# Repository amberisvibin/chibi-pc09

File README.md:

# chibi pc-09

## Archived!

This repo has been archived, and the different parts have been migrated to other repos.

The PCB for prototype 1 has been moved to https://gitea.ambersplace.net/chibi/pc09-prototype-1

The firmware has been moved to https://gitea.ambersplace.net/chibi/chibi-firmware

## Description

The PC-09 will be a 6309 based microcomputer with an MMU using 74HC670 register files and dual 16550 UARTs. The plan is to eventually add uPD7220 graphics and PS/2 mouse and keyboard.

The two 74HC670s will take the top 4 bits of the address bus and expand them to 8 bits, turning the 16 bit cpu address space into a 20 bit address space capable of addressing 1MB of memory. Memory pages are 4KB. Being a register file, any page can be mapped to any slot, allowing complex memory management schemes.

The 16550 UART is capable of interrupt driven operation with FIFOs, allowing for characters to be processed in batches rather than individually, minimizing task switch delays. They also support hardware flow control, and some versions can automatically assert RTS when the FIFO is nearing full.

The uPD7220 graphics are very powerful, allowing 16 colors at 640x480, but it is a complex chip to get working. It will be left for a later date.

The solution for PS/2 keyboard and mouse have not yet been decided.

## Progress

I had started wiring together a board for prototyping, but it was destroyed in hurricane Helene. I am now recreating it in schematic form in order to order a PCB.

Prototype 1 is currently in progress. It will be a much simpler system. It will have no MMU, just the CPU, some RAM, some ROM, and the UART.

The PCB and parts for Prototype #1 have been ordered, and assembly will begin soon. Initial test code is now available in the code/ directory.

Assembly is in progress.

## License

This project is licensed under the MIT license. This applies to both the hardware (schematics, bill of materials, pcb layouts) and documentation. This does *not* apply to the datasheets/ directory or code/assist09/. Those files belong to their respective copyright holders.

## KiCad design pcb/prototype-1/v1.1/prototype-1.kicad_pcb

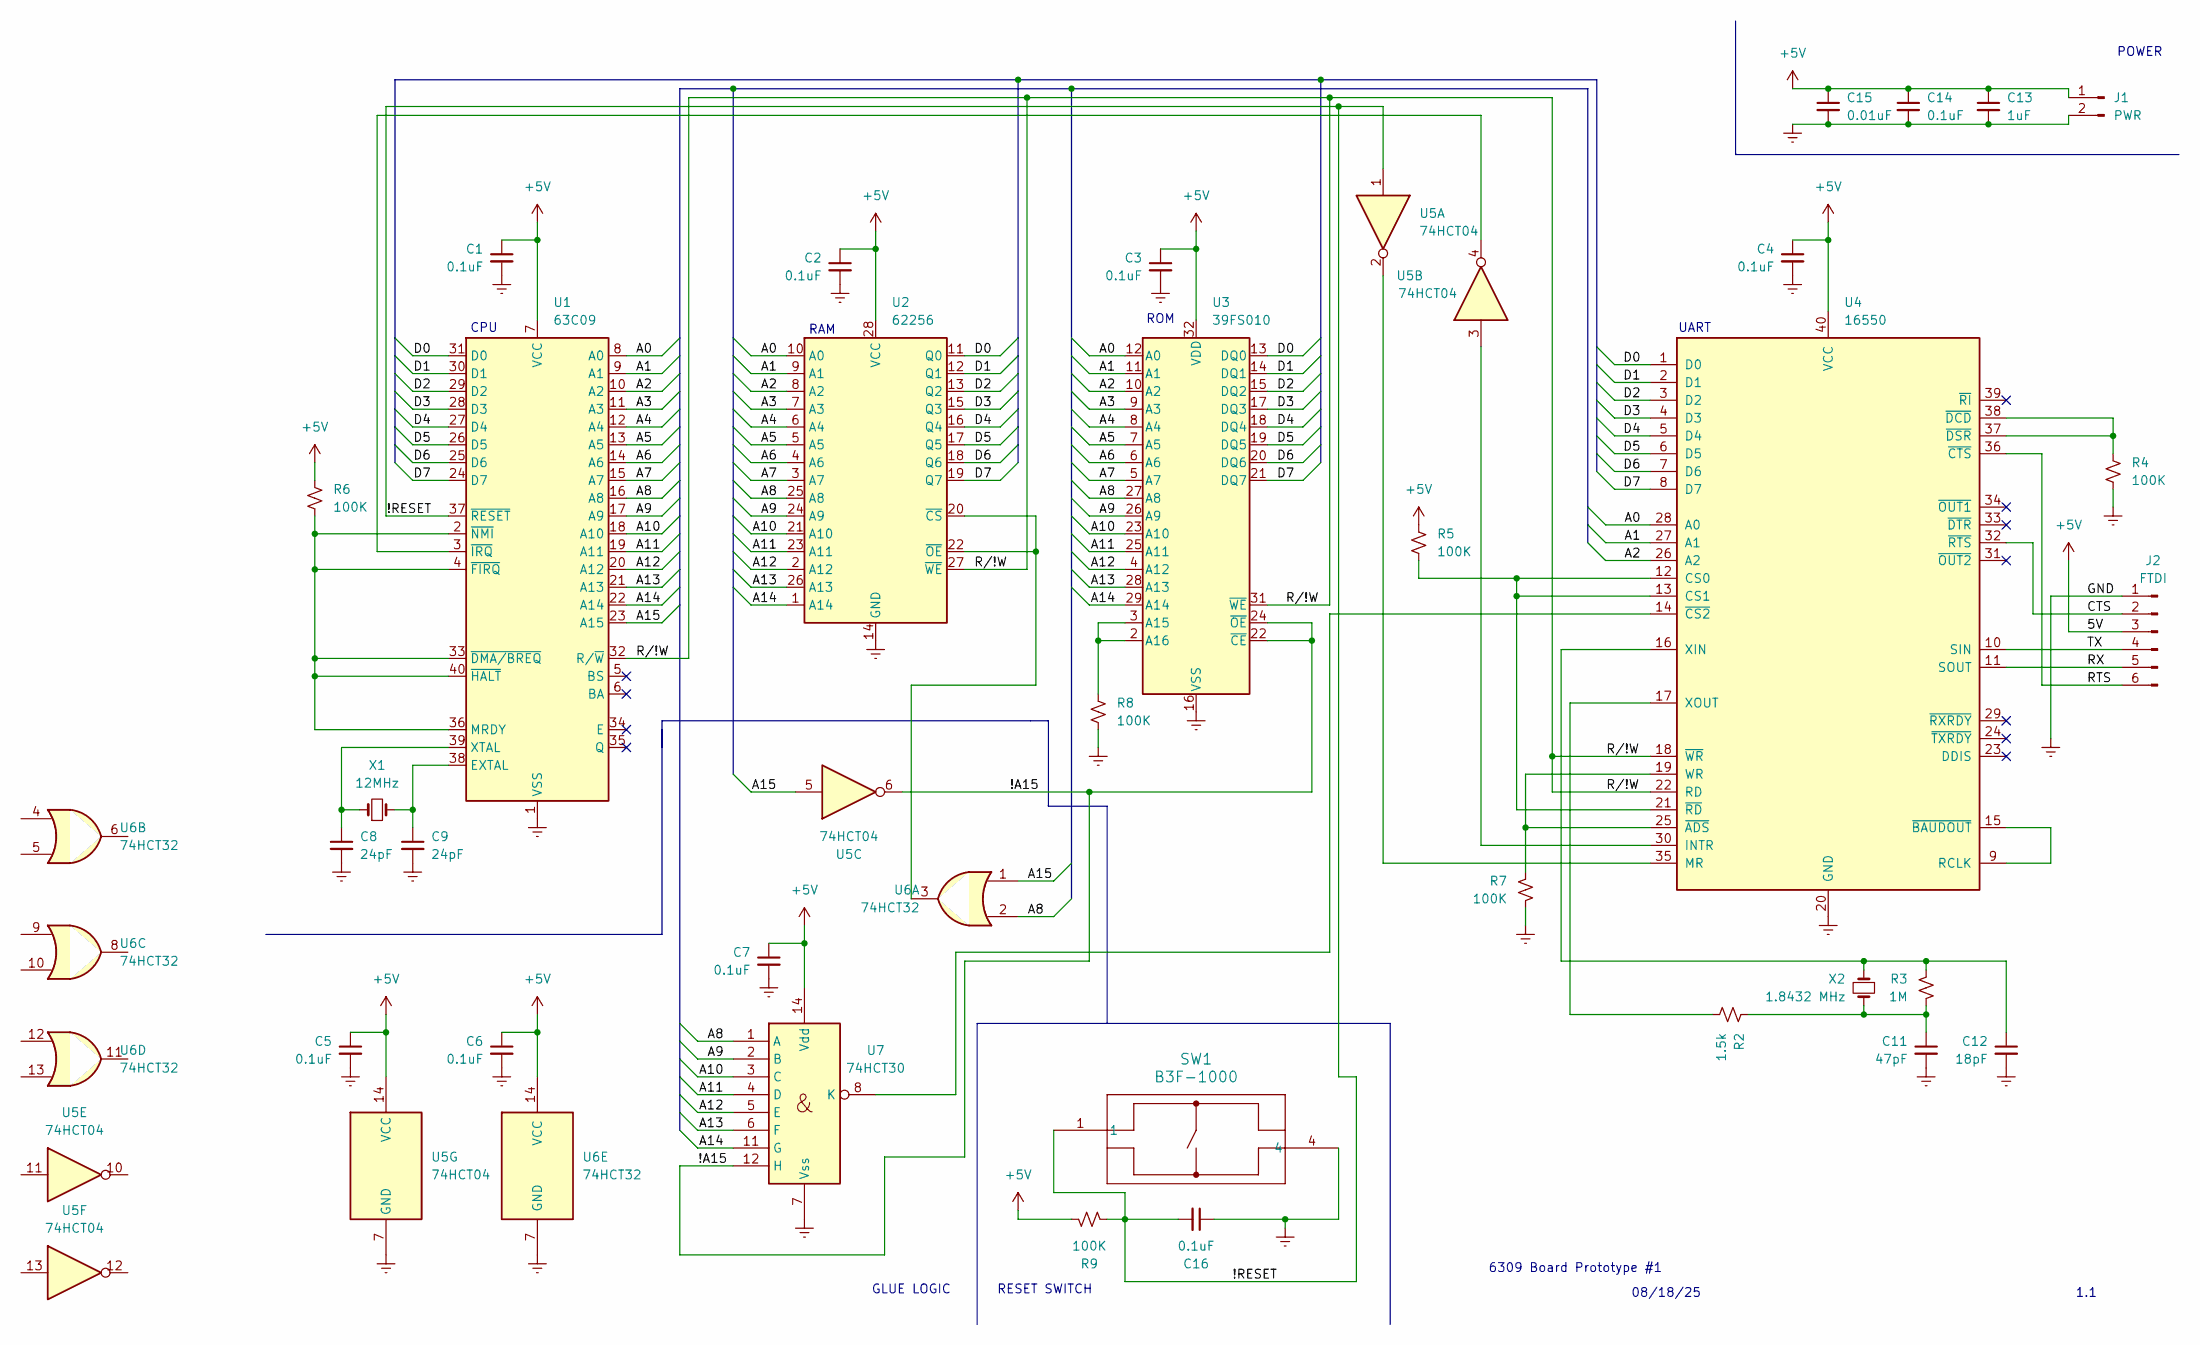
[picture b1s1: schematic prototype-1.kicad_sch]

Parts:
C1, C2, C3, C4, C5, C6, C7, C14, C16: 0.1uF; CAP_C320C_MR_X7R_KEM
C8, C9: 24pF; CAP_C317_KEM
C11: 47pF; C_Disc_D5.0mm_W2.5mm_P5.00mm
C12: 18pF; CAP_C317_KEM
C13: 1uF; CAP_C330C_MR_X7R_KEM
C15: 0.01uF; CAP_C315C_MR_X7R_KEM
J1: PWR; PinHeader_1x02_P2.54mm_Vertical
J2: FTDI; PinHeader_1x06_P2.54mm_Vertical
R2: 1.5k; R_Axial_DIN0207_L6.3mm_D2.5mm_P5.08mm_Vertical
R3: 1M; R_Axial_DIN0207_L6.3mm_D2.5mm_P5.08mm_Vertical
R4, R5, R6, R7, R8, R9: 100K; R_Axial_DIN0207_L6.3mm_D2.5mm_P5.08mm_Vertical
SW1: B3F-1000; SW_B3F-1000_OMR
U1: 63C09; DIP-40_W15.24mm_Socket
U2: 62256; DIP-28_W15.24mm_Socket
U3: 39FS010; DIP-32_W15.24mm
U4: 16550; DIP-40_W15.24mm_Socket
U5: 74HCT04; DIP-14_W7.62mm_Socket
U6: 74HCT32; DIP-14_W7.62mm_Socket
U7: 74HCT30; DIP-14_W7.62mm_Socket
X1: 12MHz; Crystal_HC49-U_Vertical
X2: 1.8432 MHz; Crystal_HC49-U_Vertical

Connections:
+5V: C1.1, C2.1, C3.1, C4.1, C5.1, C6.1, C7.1, C13.1, C14.1, C15.1, J1.1, J2.3, R5.2, R6.2, R9.2, U1.7 (VCC), U2.28 (VCC), U3.32 (VDD), U4.40 (VCC), U5.14 (VCC), U6.14 (VCC), U7.14 (Vdd)
/!A15: U3.22 (~CE), U3.24 (~OE), U5.6, U7.12 (H)
/!RESET: C16.2, R9.1, SW1.1, U1.37 (~RESET), U5.1
/A0: U1.8 (A0), U2.10 (A0), U3.12 (A0), U4.28 (A0)
/A1: U1.9 (A1), U2.9 (A1), U3.11 (A1), U4.27 (A1)
/A2: U1.10 (A2), U2.8 (A2), U3.10 (A2), U4.26 (A2)
/A3: U1.11 (A3), U2.7 (A3), U3.9 (A3)
/A4: U1.12 (A4), U2.6 (A4), U3.8 (A4)
/A5: U1.13 (A5), U2.5 (A5), U3.7 (A5)
/A6: U1.14 (A6), U2.4 (A6), U3.6 (A6)
/A7: U1.15 (A7), U2.3 (A7), U3.5 (A7)
/A8: U1.16 (A8), U2.25 (A8), U3.27 (A8), U6.2, U7.1 (A)
/A9: U1.17 (A9), U2.24 (A9), U3.26 (A9), U7.2 (B)
/A10: U1.18 (A10), U2.21 (A10), U3.23 (A10), U7.3 (C)
/A11: U1.19 (A11), U2.23 (A11), U3.25 (A11), U7.4 (D)
/A12: U1.20 (A12), U2.2 (A12), U3.4 (A12), U7.5 (E)
/A13: U1.21 (A13), U2.26 (A13), U3.28 (A13), U7.6 (F)
/A14: U1.22 (A14), U2.1 (A14), U3.29 (A14), U7.11 (G)
/A15: U1.23 (A15), U5.5, U6.1
/CTS: J2.2, U4.32 (~RTS)
/D0: U1.31 (D0), U2.11 (Q0), U3.13 (DQ0), U4.1 (D0)
/D1: U1.30 (D1), U2.12 (Q1), U3.14 (DQ1), U4.2 (D1)
/D2: U1.29 (D2), U2.13 (Q2), U3.15 (DQ2), U4.3 (D2)
/D3: U1.28 (D3), U2.15 (Q3), U3.17 (DQ3), U4.4 (D3)
/D4: U1.27 (D4), U2.16 (Q4), U3.18 (DQ4), U4.5 (D4)
/D5: U1.26 (D5), U2.17 (Q5), U3.19 (DQ5), U4.6 (D5)
/D6: U1.25 (D6), U2.18 (Q6), U3.20 (DQ6), U4.7 (D6)
/D7: U1.24 (D7), U2.19 (Q7), U3.21 (DQ7), U4.8 (D7)
/RTS: J2.6, U4.36 (~CTS)
/RX: J2.5, U4.11 (SOUT)
/R/!W: U1.32 (R/~W), U2.27 (~WE), U3.31 (~WE), U4.18 (~WR), U4.22 (RD)
/TX: J2.4, U4.10 (SIN)
GND: C1.2, C2.2, C3.2, C4.2, C5.2, C6.2, C7.2, C8.2, C9.2, C11.2, C12.2, C13.2, C14.2, C15.2, C16.1, J1.2, J2.1, R4.1, R7.1, R8.1, SW1.4, U1.1 (VSS), U2.14 (GND), U3.16 (VSS), U4.20 (GND), U5.7 (GND), U6.7 (GND), U7.7 (Vss)
unnamed: C11.1, R2.1, R3.2, X2.2
unnamed: C9.1, U1.38 (EXTAL), X1.2
unnamed: R6.1, U1.2 (~NMI), U1.4 (~FIRQ), U1.33 (~DMA/BREQ), U1.36 (MRDY), U1.40 (~HALT)
unnamed: C8.1, U1.39 (XTAL), X1.1
unnamed: U1.3 (~IRQ), U5.4
unnamed: U2.20 (~CS), U2.22 (~OE), U6.3
unnamed: R8.2, U3.2 (A16), U3.3 (A15)
unnamed: R5.1, U4.12 (CS0), U4.13 (CS1), U4.21 (~RD)
unnamed: U4.30 (INTR), U5.3
unnamed: U4.35 (MR), U5.2
unnamed: U4.9 (RCLK), U4.15 (~BAUDOUT)
unnamed: R7.2, U4.19 (WR), U4.25 (~ADS)
unnamed: C12.1, R3.1, U4.16 (XIN), X2.1
unnamed: R2.2, U4.17 (XOUT)
unnamed: U4.14 (~CS2), U7.8 (K)
unnamed: R4.2, U4.37 (~DSR), U4.38 (~DCD)

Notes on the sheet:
GLUE LOGIC
1.1
ROM
UART
CPU
RESET SWITCH
POWER
6309 Board Prototype #1
08/18/25
RAM

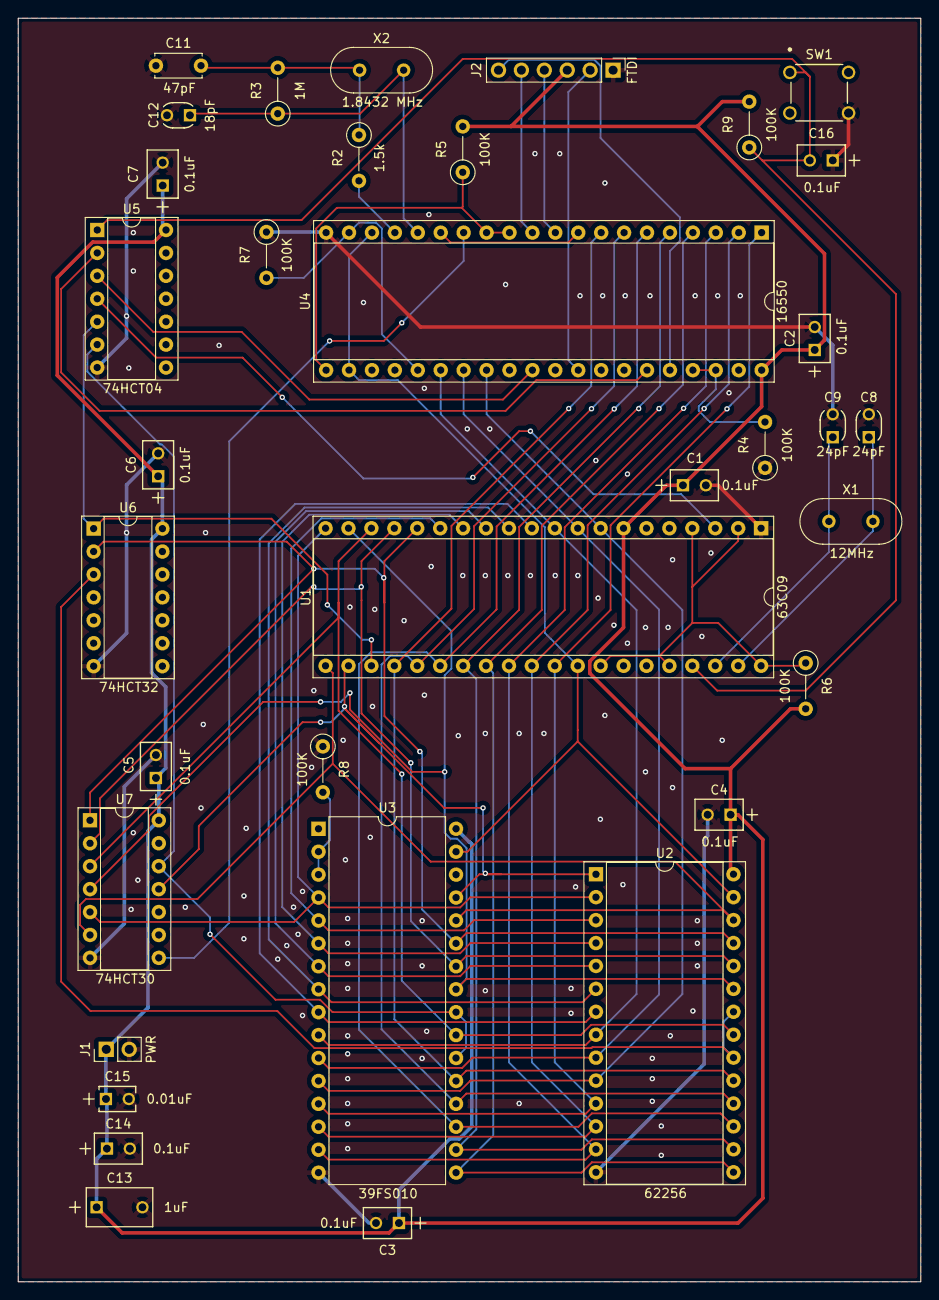
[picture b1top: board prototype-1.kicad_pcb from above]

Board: 2 copper layers, 100.0 x 140.0 mm, 35 parts (0 on the bottom side), 49 nets.

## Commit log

2020-04-17 created proper window, added menu bar, got pixel by pixel control of window
2020-04-17 program file initial commit
2020-04-23 character write working
2020-04-23 re configured GTK to be much easier we now have a function that runs every draw
2020-04-23 the function does not run every frame, just on every draw. fixed a few things
2020-04-28 a hell of a lot changed. ported from gtk to sdl added entire font added keyboard control added cursor
    TODO: backspace works on every char of every line, make aware of newline
    add colour to drawChar
2020-05-05 got print working, new keyboard control converts keycode to char. all chars conv to charcodes using shiftMap and charMap. added temp cp/m logo cause fuck it
2020-05-14 Create simple desc
2020-05-15 update readme to reflect name and purpose change
2020-05-15 copy all local files to repo
    cp/m files, sprites, circuit design
2020-05-15 c++ folder
2020-05-15 move license and readme back to root, oops
2020-05-15 add name
2020-05-15 add missing ')'
2020-05-15 test GPG signing
2020-05-15 remove GPG key test
2020-05-15 realized the emulators were not mine, cant be in the repo
2020-05-15 c++ was a submodule instead of a folder, renamed to emu
2020-05-15 remove SN74LS273NE4
    contains useless samacys libraries
2020-05-15 make readme for z80screentest
2020-05-15 move z80screentest security file to folder
2020-05-15 move z80screentest to sperate repo to make submodule
2020-05-15 make z80screentest a submodule
2020-05-15 remove empty folder
2020-05-15 Removed submodule z80screentest
2020-05-15 re add submodule, i messed it up and had to revert
2020-05-15 more organization, again :\
2020-05-15 logo and first version of schematic
2020-05-15 update z80screentest to latest
2020-05-16 add new modes
2020-05-16 add extra boot, i/o, and gfx info
2020-05-16 add double buffer info
2020-05-16 make WIP more clear
2020-05-26 design notes
2020-05-26 fixed formatting
2020-05-26 update readme with new info
2020-05-26 clarify bootfile info
2020-05-26 add max ram
2020-06-08 new design docs
    i should probably type these up at some point.
2020-06-08 more detail on graphics
2020-08-26 rem useless emu folder
2020-09-15 add commit activity
2020-09-15 update to reflect 6809
2020-09-15 more detail
2020-09-15 add code of conduct badge
2020-09-15 fix CODE_OF_CONDUCT link
2020-09-15 rem commit activity badge - works erratically
2020-09-15 add code of conduct section
2020-09-15 file no longer useful
2020-10-21 add nitros-9 link
2021-05-08 add in new tech specs
2021-05-08 update readme to reflect design decisions
2021-05-08 cleanup and condensing readme
2021-05-08 fix naming inconsistency in readme
2021-05-08 add more detail to tech specs
2021-05-13 start work on schematics
2021-05-18 os-9 mockups
2021-05-18 remove outdated mockups
2021-05-19 delete gpl license
    GPL requires all works using this work be GPL compatible. I would rather allow my work to be used by all, even commercially. the MPL allows my work to be used commercially, as long as my work is stil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
2021-05-19 add MPL
2021-05-21 chibi logo
2021-09-21 add screenshot
2021-09-21 add sprite/320x200_os9_mockup-logo_rainbow_2x.png
2021-09-21 change screenshot to smaller file
2022-11-29 docs on using ti mmu, unfinished
2023-07-06 datasheets
2023-07-15 vga upd7220
2024-10-21 remove stupid contributor thing, change license to MIT
2024-10-21 add/remove datasheets
2024-10-21 remove html thing i dont remember
2024-10-21 edit docs readme, stop ghostwriter from shitting files everywhere
2024-10-21 remove old schematics, add new ones
2024-10-21 add new proto img, remove contributor covenant badge
2024-10-22 new datasheets, some vga stuff
2024-10-22 rename/edit docs and remove old scans
2024-10-22 updated readme to current plans
2024-10-22 fix readme newlines
2024-10-23 add 16550 link, update readme, schematic work
2024-10-23 actually update the readme
2024-10-23 VT82C42 info, schematic work. considering moving to cans
2024-10-23 jameco order list. i thought it would go better
2024-10-23 fix typo in links.txt
2024-10-23 reset switch
2024-10-23 set up serial port, new link
2024-10-24 clarify license in readme
2024-10-24 mmu info
2024-10-24 mmu datasheet
2024-10-24 organization
2024-10-24 clocks on sch, 6809 datasheet, jameco xtals
2024-10-24 new datasheets, sch work, memory map
2024-10-24 almost done with schematic
2024-10-24 add footprints to schematic
2024-10-24 new proto photo
2024-10-28 changed rom, added correct switch, added a million footprints
2024-10-28 fix readme typo
2024-10-28 new output image
2024-10-31 switch from Tl16C550 to PC16550D due to availability
2024-10-31 fixed schematic, started pcb
2024-10-31 pcb work
2024-11-01 schematic work
2024-11-05 pcb work, again
2024-11-06 schematic work once again, getting close
2024-11-08 fixed CTS/RTS and doubled width of power traces
2024-11-14 pcb design finished, need to get reviewed
2024-11-14 move photos
2024-11-14 generate output files
2024-11-14 add silkscreen text, re generate gerbers
2024-11-14 fix dumbass mistake, re generate
2024-11-15 remove excess vias
2024-11-15 fix DRC errors
2024-11-15 add ground connection to decoupling cap
2024-11-19 add potential vram datasheet
2024-11-19 add potential clock chip datasheet, fix gerber
2024-11-19 folder and such for coding
2024-11-19 added books for programming
2024-11-21 start working on boot code, move things around
2024-11-21 minimum functional bootcode
2024-11-21 trying to get the linker script to work
2024-11-21 chore: clean old binaries in prep for gitignore
2024-11-21 chore: renamed source file to move it to src dir
2024-11-21 chore: added gitignore file
2024-11-21 chore: added editorconfig file
2024-11-21 chore: added makefile
2024-11-21 chore: completed missing parts of makefile.
2024-11-21 chore: fixed empty echo in makefile.
2024-11-21 chore: added build/ to gitignore.
2024-11-22 chore: migrated to asm6809
2024-11-22 clean: removed old files from lwtools era
2024-11-22 chore: changing instances of Chibi PC-09 to CHIBI PC-09.
2024-11-22 doc: sane outline for docs and how to build the firmware.
2024-11-22 fix: use a version of assist09 that is compatible with asm6809
2024-11-22 docs: update code README to reflect changes and update main README with new update
2024-11-22 chore: remove old docs, clean up font stuff
2024-11-22 docs: update directories in README
2024-11-22 chore: organize pcb files
2024-11-22 style: prettier math (thx asm6809), add MIT license to boot.s, remove stray (
2024-11-28 feat: add hardware.inc
2024-11-28 refactor: made preparations for hardware.inc.
2024-11-28 fix: broken whitespace expected by asm6809.
2024-11-28 style: moved comments to the side
2024-11-28 fix: now tracking incs in makefile.
2024-11-29 chore: added ROM_BASE and VECS_BASE to hardware.inc
2024-11-29 style: removed pointless newline
2024-11-29 chore: added SRAM_BASE to hardware.inc.
2024-11-29 fix: added vim ft=asm to inc file.
2024-11-29 chore: added .inc to editorconfig rules.
2024-11-29 chore: added flag for 8n1 serial
2024-11-29 fix: fixed immediate values
2024-12-05 feat(hardware.inc): added flags for LCR, MCR, and LSR.
2024-12-05 feat(hardware.inc): added flags for MSR.
2024-12-05 feat(hardware.inc): added flags for IER and changed 'Modem'->'MODEM'
2024-12-05 feat(hardware.inc): Added flags for IIR
2024-12-05 feat(hardware.inc): Added flags for FCR
2024-12-05 fix: register name, comment spacing
2024-12-07 chore: using aliases from hardware.inc and optimized divisor setup
2024-12-07 feat: new serial functions
2024-12-11 style: caps in comment fix
2024-12-11 feat: ported ROBIT-2 for MIKBUG to CHIBI PC-09
2024-12-11 refactor(memtest): refactored the port of ROBIT-2
2024-12-16 docs: add 74hc670 datasheet, potential replacement for 74ls612
2025-08-01 update readme to reflect changes
2025-08-01 add badge for gitea
2025-08-18 Add The 6309 Book
2025-08-18 new pcb rev, fixes reset switch error
2025-08-21 new pcb cleanup
2025-08-21 clean up datasheets/ and remove outdated files
2025-08-21 remove old data from docs/
2025-08-22 fix boot firmware README
2025-08-31 feat\!: migrate to LWTOOLS build system
2025-08-31 feat: modularized with lwtools build system
2025-09-02 Adjusted code/boot/makefile to remove map.txt when make clean is run
2025-10-07 archive notice
